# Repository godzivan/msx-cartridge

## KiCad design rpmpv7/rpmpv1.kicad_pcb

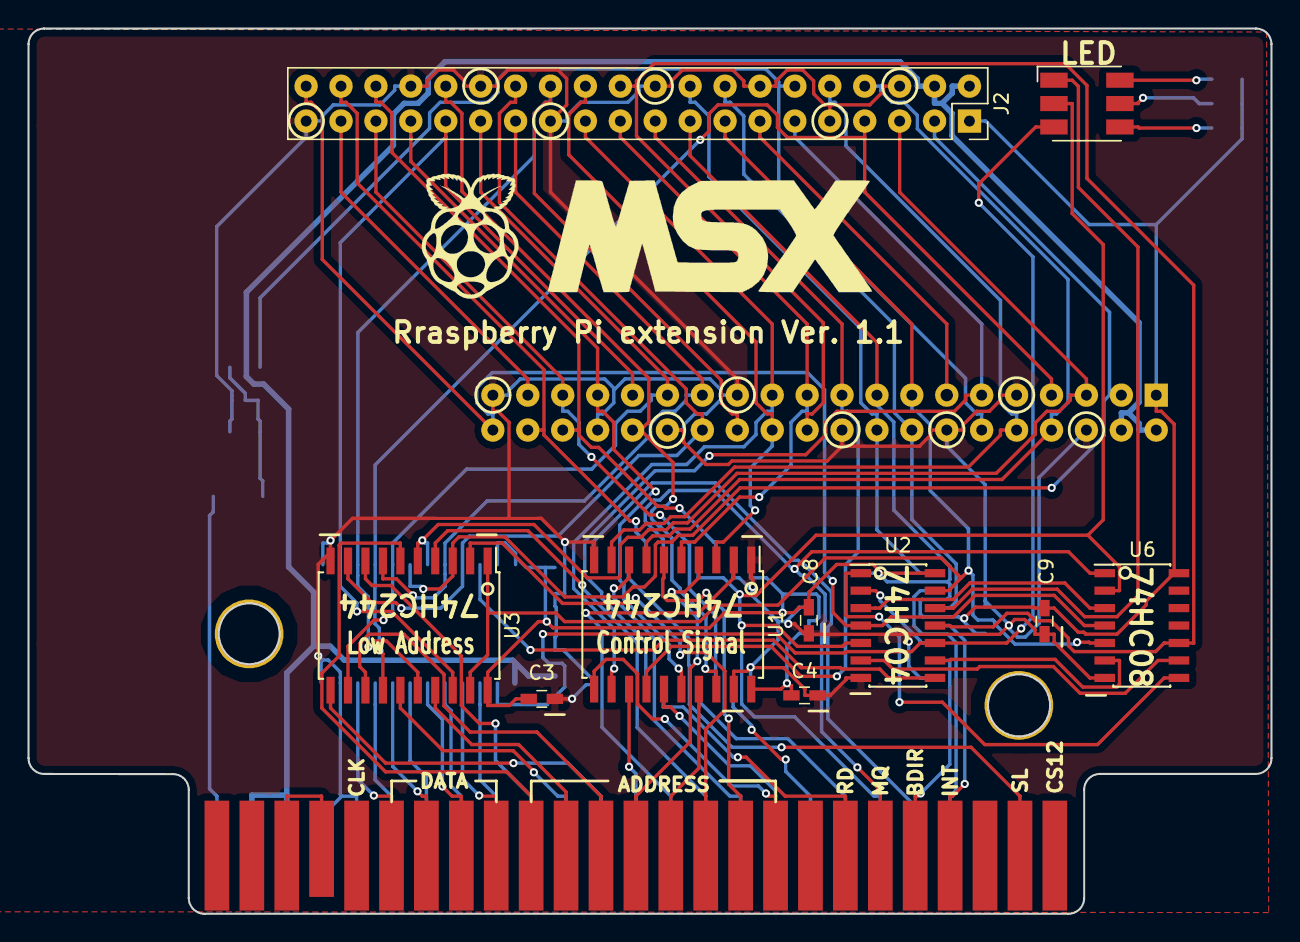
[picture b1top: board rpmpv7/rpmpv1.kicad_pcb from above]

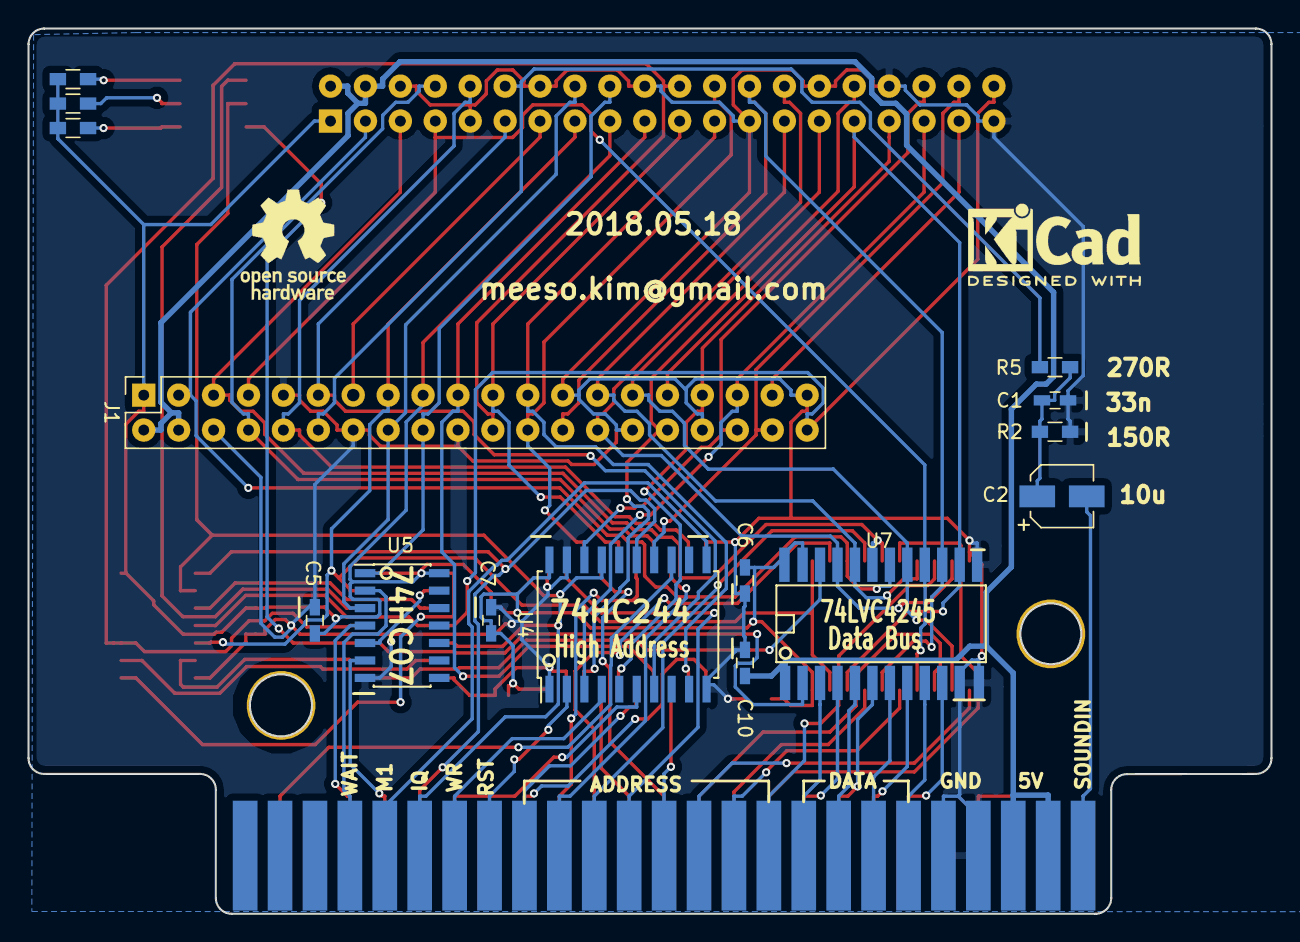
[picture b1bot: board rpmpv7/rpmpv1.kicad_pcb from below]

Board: 2 copper layers, 90.4 x 64.4 mm, 29 parts (17 on the bottom side), 79 nets.

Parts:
C1, C3, C4, C5, C6, C7, C8, C9, C10: C; C_0603_HandSoldering
C2: CP; CP_Elec_4x4.5
D1: LED_RGB; LED_RGB_5050-6
G1: LOGO; raspberry_pi_logo
J1, J2: RPi_GPIO; Socket_Strip_Straight_2x20_Pitch2.54mm
P1: CONN_02X25; card_edge_connector
R1, R2, R3, R4, R5: R; R_0603_HandSoldering
REF2: OSHW-Logo_7.5x8mm_SilkScreen
REF3: KiCad-Logo2_6mm_SilkScreen
U1, U3, U4: 74HC244; SOIC-20W_7.5x12.8mm_Pitch1.27mm
U2: 74HC04; SOIC-14_3.9x8.7mm_Pitch1.27mm
U5: 74LS07; SOIC-14_3.9x8.7mm_Pitch1.27mm
U6: 74LS08; SOIC-14_3.9x8.7mm_Pitch1.27mm
U7: LVC4245; SOIC-24@

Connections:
+3V3: C3.1, C4.1, C5.1, C6.1, C7.1, C8.1, C9.1, J1.1, J1.17, J2.1, J2.17, R1.1, R3.1, R4.1, U1.20, U2.14, U3.20, U4.20, U5.14, U6.14, U7.23, U7.24
+5V: C10.2, J1.2, J1.4, J2.2, J2.4, P1.45, P1.47, U7.1
/A0: P1.28, U3.13
/A1: P1.27, U3.11
/A2: P1.30, U3.17
/A3: P1.29, U3.15
/A4: P1.32, U3.6
/A5: P1.31, U3.8
/A6: P1.22, U3.2
/A7: P1.21, U3.4
/A8: P1.24, U1.17
/A9: P1.17, U1.15
/A10: P1.20, U1.6
/A11: P1.19, U1.8
/A12: P1.23, U1.2
/A13: P1.26, U1.4
/A14: P1.25, U1.13
/A15: P1.18, U1.11
/ATN: J1.40, J2.40, U2.4, U6.4
/BDIR: U2.2, U5.5
/BUSDIR: P1.10, U5.6
/D0: P1.34, U7.4
/D1: P1.33, U7.3
/D2: P1.36, U7.6
/D3: P1.35, U7.5
/D4: P1.38, U7.8
/D5: P1.37, U7.7
/D6: P1.40, U7.10
/D7: P1.39, U7.9
/DAT_DIR: D1.3, U2.10, U7.2
/DAT_EN: U2.8, U7.22
/INT: P1.8, U5.4
/IORQ: D1.2, P1.11, U2.5, U4.17, U6.2
/M1: P1.9, U4.11
/MREQ: P1.12, U4.15, U6.1
/RA8: J1.24, J2.24, U1.3
/RA9: J1.21, J2.21, U1.5
/RA10: J1.19, J2.19, U1.14
/RA11: J1.23, J2.23, U1.12
/RA12: J1.32, J2.32, U1.18
/RA13: J1.33, J2.33, U1.16
/RA14: J1.8, J2.8, U1.7
/RA15: J1.10, J2.10, U1.9
/RATN: J1.15, J2.15, U2.13, U3.1, U3.19, U6.5
/RC16: J1.36, J2.36, U4.18
/RC17: J1.11, J2.11, U4.7
/RC18: J1.12, J2.12, R5.1
/RC19: J1.35, J2.35, U4.3
/RC20: J1.38, J2.38, U4.14
/RC23: J1.16, J2.16, U5.3
/RC24: J1.18, J2.18, U5.1
/RC25: J1.22, J2.22, U2.11, U6.10
/RC26: J1.37, J2.37
/RC27: J1.13, J2.13
/RD: P1.14, U4.6
/RD0: J1.27, J2.27, U3.7, U7.20
/RD1: J1.28, J2.28, U3.9, U7.21
/RD2: J1.3, J2.3, U3.3, U7.18
/RD3: J1.5, J2.5, U3.5, U7.19
/RD4: J1.7, J2.7, U3.14, U7.16
/RD5: J1.29, J2.29, U3.12, U7.17
/RD6: J1.31, J2.31, U3.18, U7.14
/RD7: J1.26, J2.26, U3.16, U7.15
/RESET: P1.15, U4.2
/SLTSL: P1.4, U4.13
/SOUNDIN: C2.2, P1.49
/WAIT: P1.7, U5.2
/WR: P1.13, U4.4
/nATN: U2.3, U6.3
/nBDIR: U2.1, U6.8
/nDAT_EN: U2.9, U6.6
/nIORQ: U2.6, U6.9
/nRATN: D1.1, U2.12
GND: C1.2, C3.2, C4.2, C5.2, C6.2, C7.2, C8.2, C9.2, C10.1, J1.6, J1.9, J1.14, J1.20, J1.25, J1.30, J1.34, J1.39, J2.6, J2.9, J2.14, J2.20, J2.25, J2.30, J2.34, J2.39, P1.41, P1.43, R2.2, U1.1, U1.10, U1.19, U2.7, U3.10, U4.1, U4.10, U4.19, U5.7, U6.7, U7.11, U7.12, U7.13
unnamed: C1.1, C2.1, R2.1, R5.2
unnamed: D1.4, R4.2
unnamed: D1.5, R3.2
unnamed: D1.6, R1.2
unnamed: P1.44, P1.46

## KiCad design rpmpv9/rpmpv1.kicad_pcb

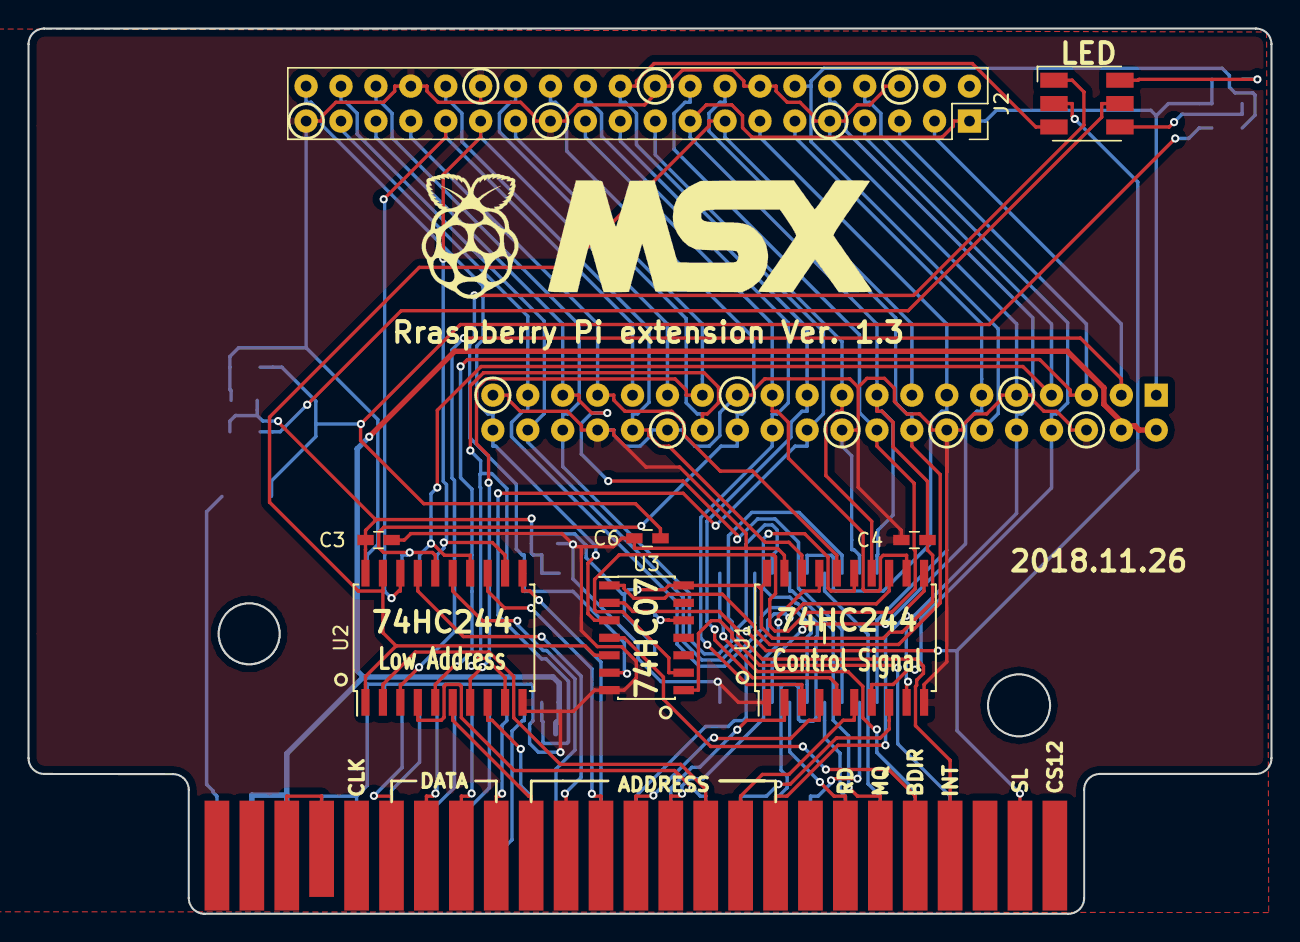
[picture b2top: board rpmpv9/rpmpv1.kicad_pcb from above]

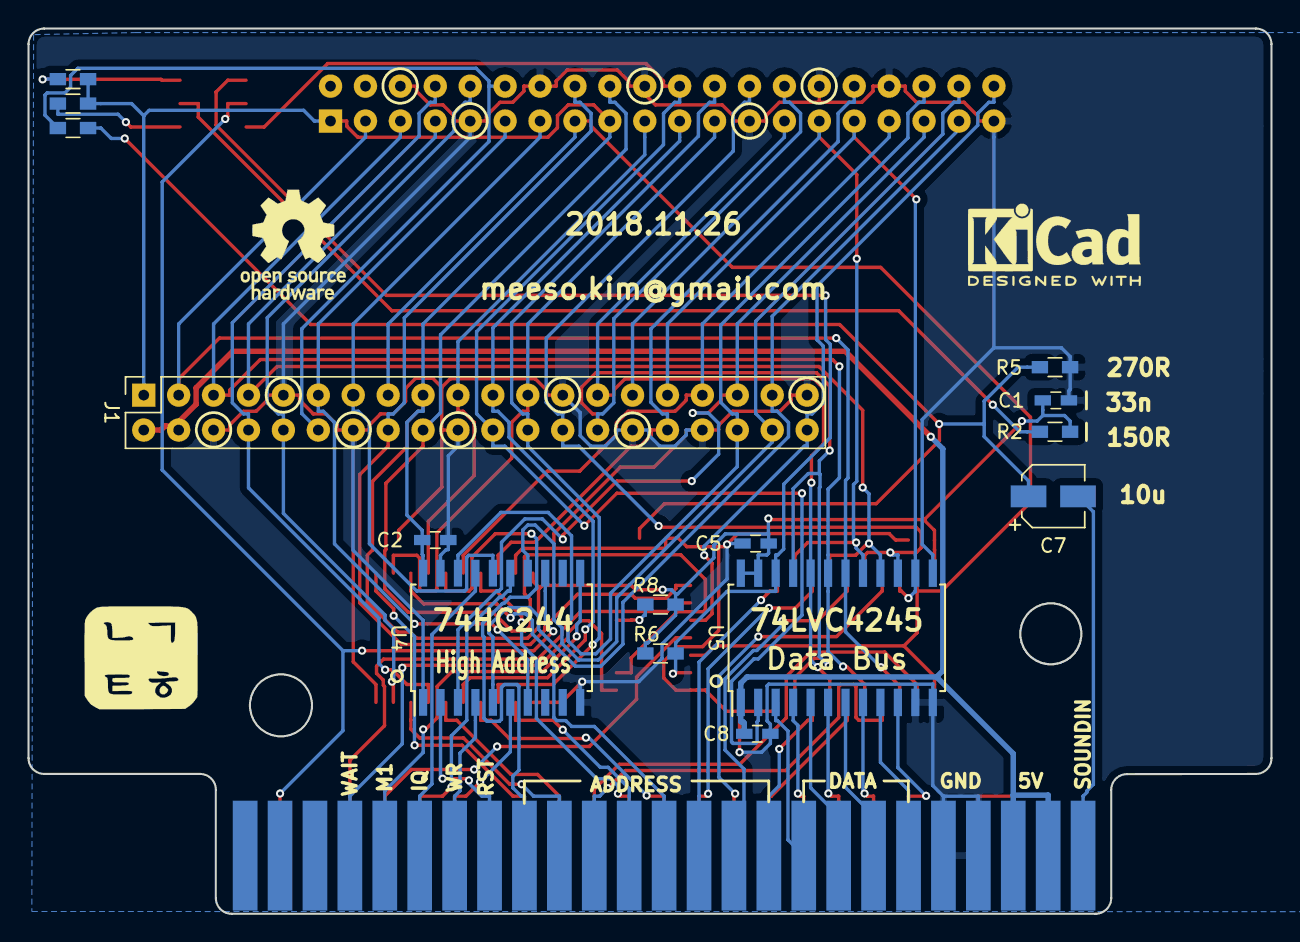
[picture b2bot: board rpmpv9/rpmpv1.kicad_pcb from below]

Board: 2 copper layers, 90.4 x 64.4 mm, 28 parts (17 on the bottom side), 73 nets.

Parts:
C1, C2, C3, C4, C5, C6, C8: C; C_0603_HandSoldering
C7: CP; CP_Elec_4x4.5
D1: LED_RGB; LED_RGB_5050-6
G1: LOGO; raspberry_pi_logo
G2: LOGO; msx-logo
J1, J2: RPi_GPIO; Socket_Strip_Straight_2x20_Pitch2.54mm
P1: CONN_02X25; card_edge_connector
R1, R2, R3, R4, R5, R6, R8: R; R_0603_HandSoldering
REF2: OSHW-Logo_7.5x8mm_SilkScreen
REF3: KiCad-Logo2_6mm_SilkScreen
U1, U2, U4: 74HC244; SOIC-20W_7.5x12.8mm_Pitch1.27mm
U3: 74LS07; SOIC-14_3.9x8.7mm_Pitch1.27mm
U5: LVC4245; SOIC-24W_7.5x15.4mm_Pitch1.27mm

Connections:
+3V3: C1.1, C2.1, C3.1, C4.1, C5.1, J1.1, J1.17, J2.1, J2.17, R1.2, R2.2, R3.2, R6.1, R8.1, U1.20, U2.20, U3.14, U4.20, U5.23, U5.24
+5V: C8.2, J1.2, J1.4, P1.45, P1.47, U5.1
/A0: P1.28, U2.13
/A1: P1.27, U2.11
/A2: P1.30, U2.17
/A3: P1.29, U2.15
/A4: P1.32, U2.6
/A5: P1.31, U2.8
/A6: P1.22, U2.2
/A7: P1.21, U2.4
/A8: P1.24, U1.17
/A9: P1.17, U1.15
/A10: P1.20, U1.6
/A11: P1.19, U1.8
/A12: P1.23, U1.2
/A13: P1.26, U1.4
/A14: P1.25, U1.13
/A15: P1.18, U1.11
/ADDR: J1.15, J2.15, U2.1, U2.19, U3.5
/BUSDIR: P1.10, U3.4
/D0: P1.34, U5.4
/D1: P1.33, U5.3
/D2: P1.36, U5.6
/D3: P1.35, U5.5
/D4: P1.38, U5.8
/D5: P1.37, U5.7
/D6: P1.40, U5.10
/D7: P1.39, U5.9
/DAT_DIR: D1.3, J1.22, J2.22, U5.2
/DAT_EN: D1.1, R6.2, U3.6, U5.22
/EXTRA: R8.2, U3.12
/INT: P1.8, U3.2
/IORQ: P1.11, U4.17
/M1: P1.9, U4.11
/MREQ: P1.12, U4.15
/RA8: J1.24, J2.24, U1.3
/RA9: J1.21, J2.21, U1.5
/RA10: J1.19, J2.19, U1.14
/RA11: J1.23, J2.23, U1.12
/RA12: J1.32, J2.32, U1.18
/RA13: J1.33, J2.33, U1.16
/RA14: J1.8, J2.8, U1.7
/RA15: J1.10, J2.10, U1.9
/RC16: J1.36, J2.36, U4.18
/RC17: J1.11, J2.11, U4.7
/RC18: J1.12, J2.12, R4.1
/RC19: J1.35, J2.35, U4.3
/RC20: J1.38, J2.38, U4.14
/RC21: J1.40, J2.40, U3.3
/RC23: J1.16, J2.16, U3.1
/RC24: J1.18, J2.18, U3.9
/RC26: J1.37, J2.37, U4.5
/RC27: J1.13, J2.13, U4.16
/RD: P1.14, U4.6
/RD0: J1.27, J2.27, U2.7, U5.20
/RD1: J1.28, J2.28, U2.9, U5.21
/RD2: J1.3, J2.3, U2.3, U5.18
/RD3: J1.5, J2.5, U2.5, U5.19
/RD4: J1.7, J2.7, U2.14, U5.16
/RD5: J1.29, J2.29, U2.12, U5.17
/RD6: J1.31, J2.31, U2.18, U5.14
/RD7: J1.26, J2.26, U2.16, U5.15
/RESET: P1.15, U4.2
/SLTSL: D1.2, P1.4, U4.13
/SOUNDIN: C7.2, P1.49
/WAIT: P1.7, U3.8
/WR: P1.13, U4.4
GND: C1.2, C2.2, C3.2, C4.2, C5.2, C6.2, C8.1, J1.6, J1.9, J1.14, J1.20, J1.25, J1.30, J1.34, J1.39, J2.6, J2.9, J2.14, J2.20, J2.25, J2.30, J2.34, J2.39, P1.41, P1.43, R5.2, U1.1, U1.10, U1.19, U2.10, U3.7, U4.1, U4.10, U4.19, U5.11, U5.12, U5.13
unnamed: C6.1, C7.1, R4.2, R5.1
unnamed: D1.4, R3.1
unnamed: D1.5, R2.1
unnamed: D1.6, R1.1
unnamed: P1.44, P1.46

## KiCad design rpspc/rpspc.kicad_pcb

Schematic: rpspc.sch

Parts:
J1: RPi_GPIO; Pin_Header_Straight_2x20_Pitch2.54mm
J2: Conn_02x17_Top_Bottom; Pin_Header_Straight_2x17_Pitch2.54mm
U1, U2: 74LS245; DIP-20_W7.62mm

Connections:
+5V: J1.2, J1.4, J2.33, U1.20, U2.20
/A0: J2.13, U1.16
/A1: J2.11, U1.17
/A2: J2.9
/A3: J2.7
/A4: J2.5
/A5: J2.3
/A6: J2.1, U1.12
/A7: J2.4
/A8: J2.6
/A9: J2.8
/A10: J2.12
/A11: J2.10, U1.18
/A12: J2.2
/CLK: J2.27, U1.13
/D0: J2.15, U2.16
/D1: J2.17, U2.14
/D2: J2.19, U2.12
/D3: J2.21, U2.11
/D4: J2.20, U2.13
/D5: J2.18, U2.15
/D6: J2.16, U2.17
/D7: J2.14, U2.18
/EXT1: J2.26, U1.14, U2.19
/RA0: J1.15, U1.4
/RA1: J1.16, U1.3
/RA2: J1.18, U1.2
/RA4: J1.22, U1.8
/RCLK: J1.12, U1.7
/RD0: J1.27, U2.4
/RD1: J1.28, U2.6
/RD2: J1.3, U2.8
/RD3: J1.5, U2.9
/RD4: J1.7, U2.7
/RD5: J1.29, U2.5
/RD6: J1.31, U2.3
/RD7: J1.26, U2.2
/RESET: J2.23, U1.15
/REXT1: J1.11, U1.6
/RRESET: J1.13, U1.5
/RWR: J1.8, U1.9
/WR: J2.31, U1.11, U2.1
GND: J1.6, J1.9, J1.14, J1.20, J1.25, J1.30, J1.34, J1.39, J2.34, U1.1, U1.10, U1.19, U2.10

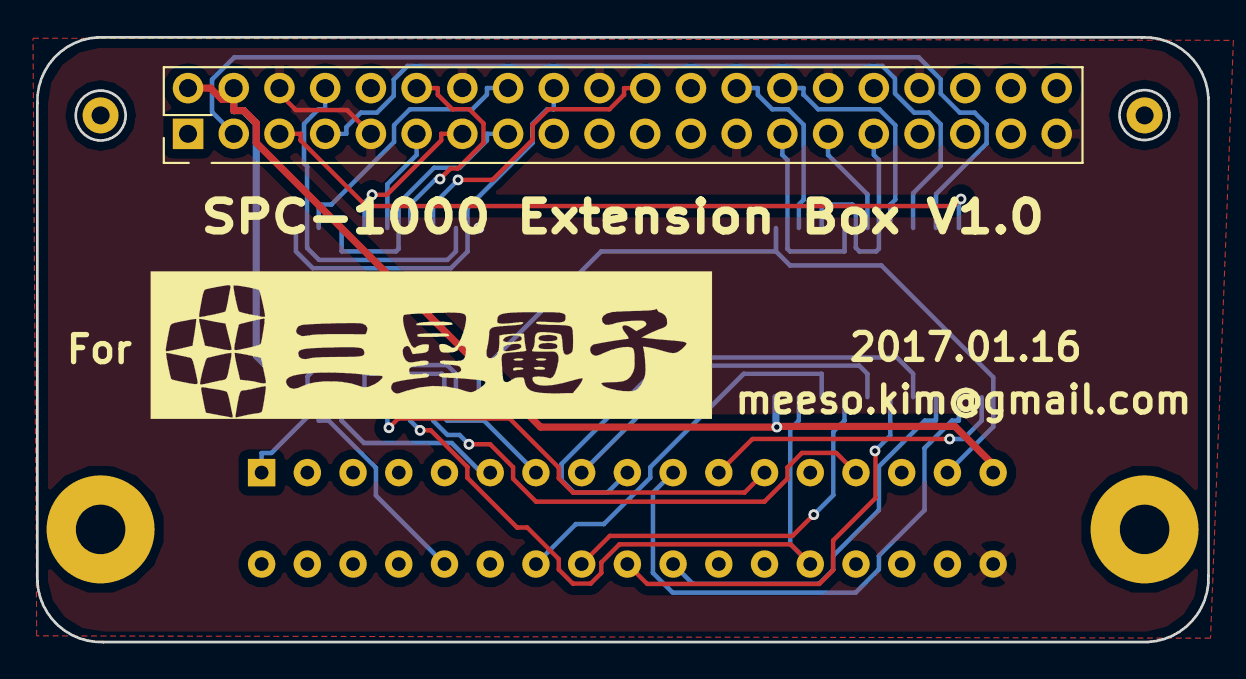
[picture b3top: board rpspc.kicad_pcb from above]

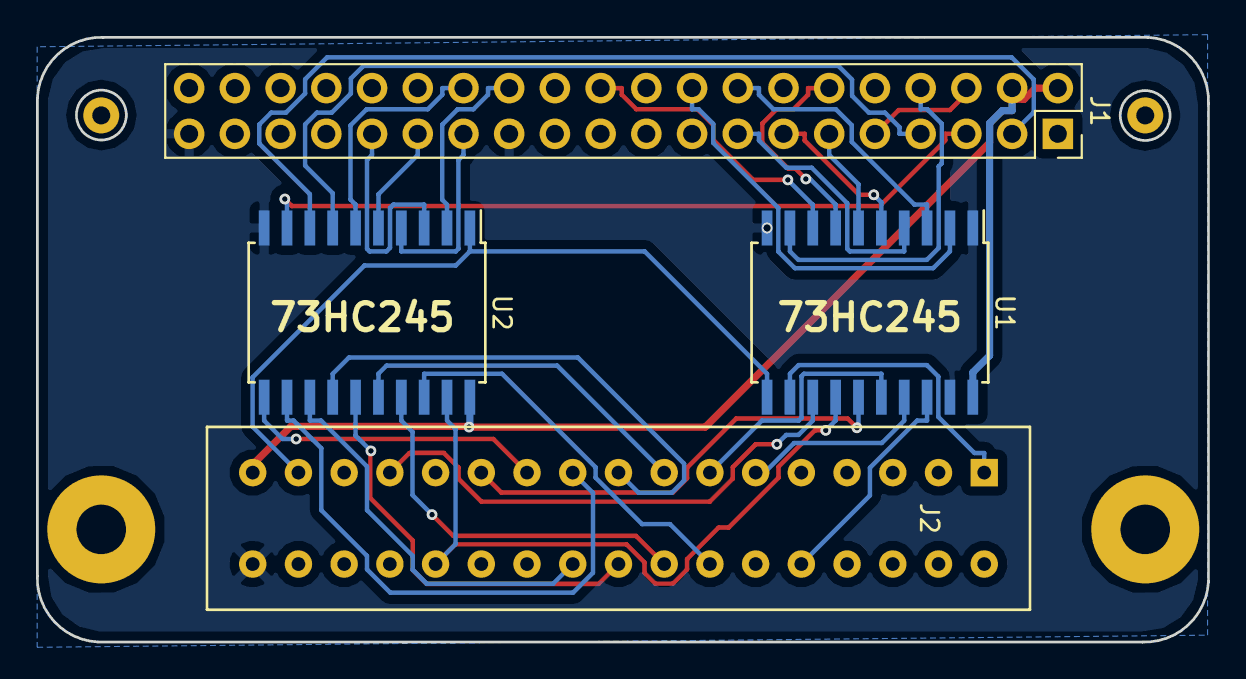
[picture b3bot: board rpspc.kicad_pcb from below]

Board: 2 copper layers, 65.1 x 33.6 mm, 4 parts (4 on the bottom side), 34 nets.

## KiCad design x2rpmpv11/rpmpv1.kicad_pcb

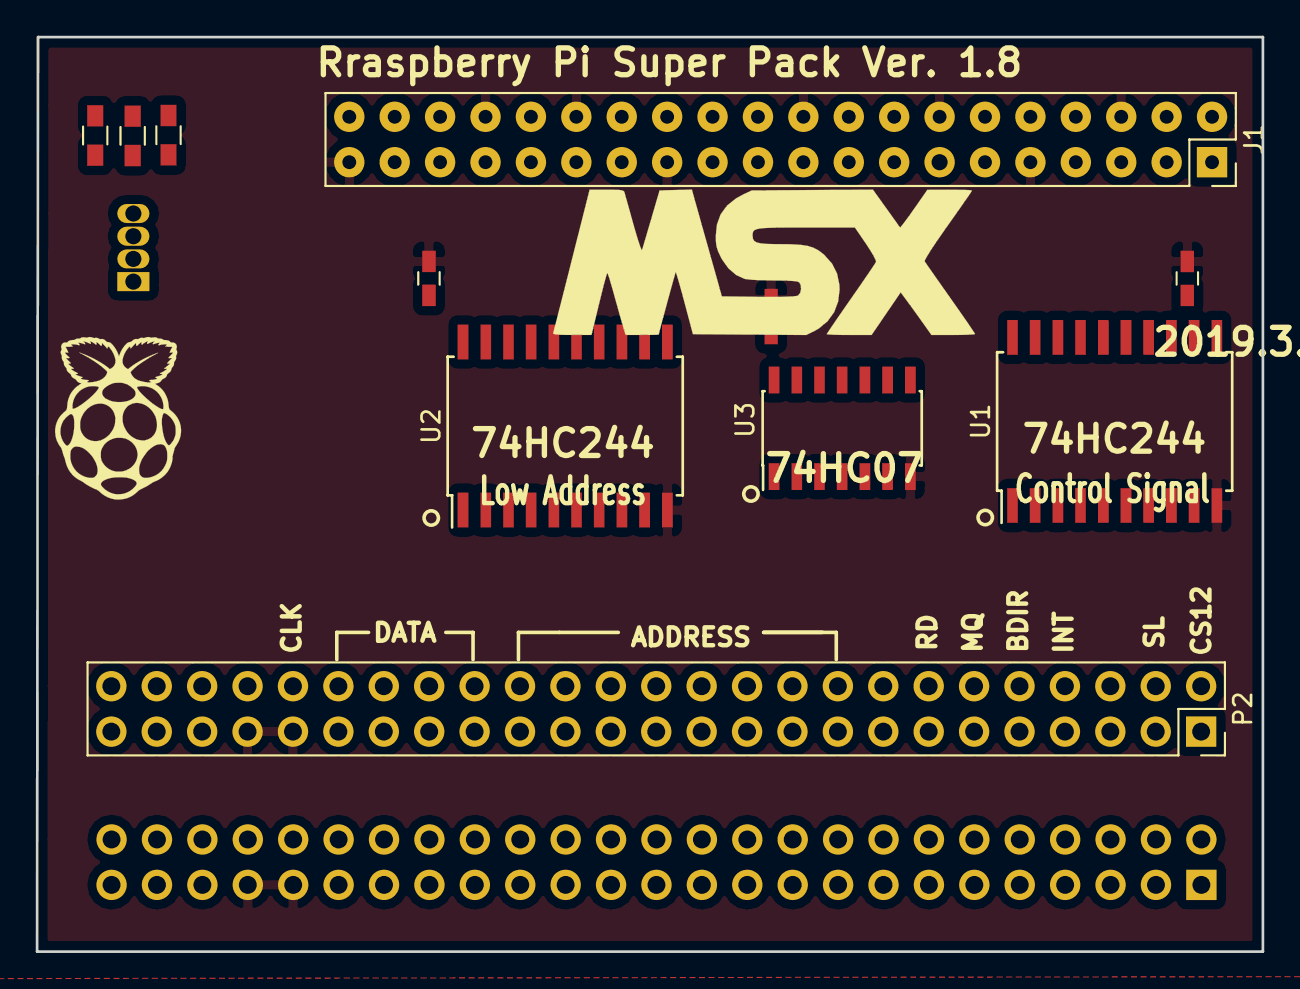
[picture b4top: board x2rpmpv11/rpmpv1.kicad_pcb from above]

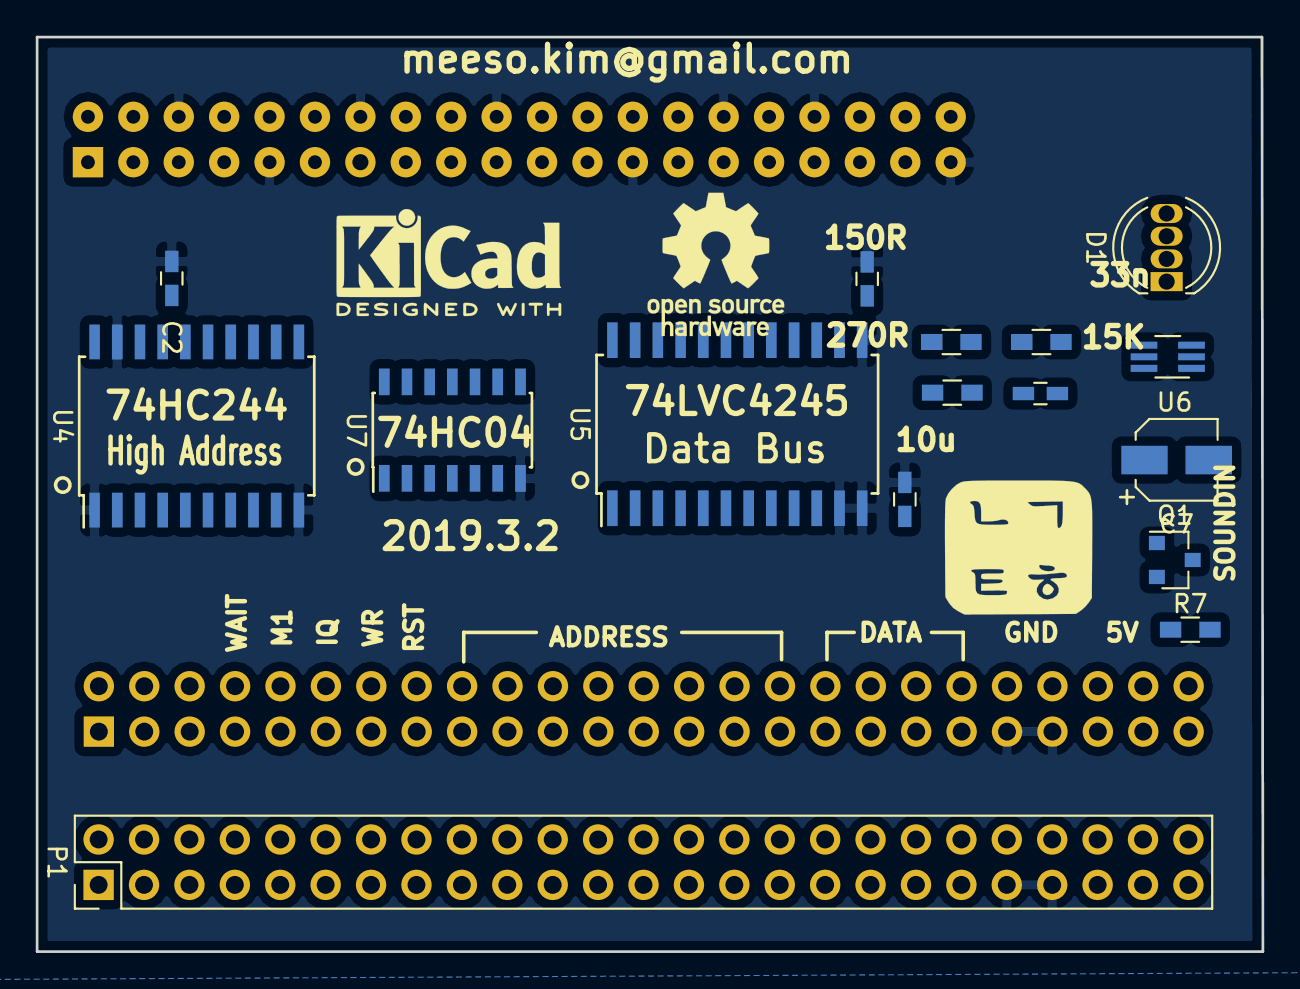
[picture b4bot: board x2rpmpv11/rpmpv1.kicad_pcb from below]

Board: 2 copper layers, 68.6 x 51.2 mm, 31 parts (18 on the bottom side), 85 nets, no tracks yet.

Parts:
C1, C2, C3, C4, C5, C6, C8: C; C_0603_HandSoldering
C7: CP; CP_Elec_4x4.5
D1: LED_RABG; LED_D5.0mm-4
G1: LOGO; raspberry_pi_logo
G2: LOGO; msx-logo
J1: RPi_GPIO; Socket_Strip_Straight_2x20_Pitch2.54mm
P1: CONN_02X25; Pin_Header_Straight_2x25_Pitch2.54mm
P2: CONN_02X25; Socket_Strip_Straight_2x25_Pitch2.54mm
Q1: Q_NPN_BEC; SOT-23
R1, R2, R3, R4, R5, R6, R7: R; R_0603_HandSoldering
REF2: OSHW-Logo_7.5x8mm_SilkScreen
REF3: KiCad-Logo2_6mm_SilkScreen
U1, U2, U4: 74HC244; SOIC-20W_7.5x12.8mm_Pitch1.27mm
U3: 74LS07; SOIC-14_3.9x8.7mm_Pitch1.27mm
U5: LVC4245; SOIC-24W_7.5x15.4mm_Pitch1.27mm
U6: NC7WZ16; SOT-363_SC-70-6_Handsoldering
U7: 74HC04; SOIC-14_3.9x8.7mm_Pitch1.27mm

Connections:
+3V3: C1.1, C2.1, C3.1, C4.1, C5.1, D1.2, J1.1, J1.17, U1.20, U2.20, U3.14, U4.20, U5.23, U5.24, U6.5, U7.14
+5V: C8.2, J1.2, J1.4, P1.45, P1.47, P2.45, P2.47, R6.1, U5.1
/12V+: P1.48, P2.48
/12V-: P1.50, P2.50
/A0: P1.28, P2.28, U2.13
/A1: P1.27, P2.27, U2.11
/A2: P1.30, P2.30, U2.17
/A3: P1.29, P2.29, U2.15
/A4: P1.32, P2.32, U2.6
/A5: P1.31, P2.31, U2.8
/A6: P1.22, P2.22, U2.2
/A7: P1.21, P2.21, U2.4
/A8: P1.24, P2.24, U1.2
/A9: P1.17, P2.17, U1.4
/A10: P1.20, P2.20, U1.6
/A11: P1.19, P2.19, U1.8
/A12: P1.23, P2.23, U1.17
/A13: P1.26, P2.26, U1.15
/A14: P1.25, P2.25, U1.13
/A15: P1.18, P2.18, U1.11
/ADDR: J1.15, U1.1, U1.19, U2.1, U2.19, U7.1
/BUSDIR: P1.10, P2.10, U3.4
/CLK: P1.42, P2.42, U4.2
/CS1: P1.1, P2.1
/CS2: P1.3, P2.3
/CS12: P1.2, P2.2
/D0: P1.34, P2.34, U5.4
/D1: P1.33, P2.33, U5.3
/D2: P1.36, P2.36, U5.6
/D3: P1.35, P2.35, U5.5
/D4: P1.38, P2.38, U5.8
/D5: P1.37, P2.37, U5.7
/D6: P1.40, P2.40, U5.10
/D7: P1.39, P2.39, U5.9
/DAT_DIR: J1.22, R3.1, U5.2
/DAT_EN: R1.1, U5.22, U7.2
/INT: P1.8, P2.8, U3.2
/IORQ: P1.11, P2.11, U4.17
/M1: P1.9, P2.9, U4.4
/MREQ: P1.12, P2.12, U4.15
/RA8: J1.24, U1.18
/RA9: J1.21, U1.16
/RA10: J1.19, U1.14
/RA11: J1.23, U1.12
/RA12: J1.32, U1.3
/RA13: J1.33, U1.5
/RA14: J1.8, U1.7
/RA15: J1.10, U1.9
/RC16: J1.36, U4.9
/RC17: J1.11, U4.7
/RC18: J1.12, U6.1
/RC19: J1.35, U4.3
/RC20: J1.38, U4.12
/RC21: J1.40, U3.3
/RC23: J1.16, U3.1
/RC24: J1.18, R2.1, U3.9
/RC26: J1.37, U4.5
/RC27: J1.13, U4.14
/RD: P1.14, P2.14, U4.8
/RD0: J1.27, U2.7, U5.20
/RD1: J1.28, U2.9, U5.21
/RD2: J1.3, U2.3, U5.18
/RD3: J1.5, U2.5, U5.19
/RD4: J1.7, U2.14, U5.16
/RD5: J1.29, U2.12, U5.17
/RD6: J1.31, U2.18, U5.14
/RD7: J1.26, U2.16, U5.15
/RESET: P1.15, P2.15, U4.11
/RFSH: P1.6, P2.6
/RSV0: P1.5, P2.5
/RSV1: P1.16, P2.16
/SLTSL: P1.4, P2.4, U4.13
/SOUNDIN: P1.49, P2.49, R7.1
/SW0: P1.44, P2.44
/SW1: P1.46, P2.46
/WAIT: P1.7, P2.7, U3.8
/WR: P1.13, P2.13, U4.6
GND: C1.2, C2.2, C3.2, C4.2, C5.2, C8.1, J1.6, J1.9, J1.14, J1.20, J1.25, J1.30, J1.34, J1.39, P1.41, P1.43, P2.41, P2.43, U1.10, U2.10, U3.7, U4.1, U4.10, U4.19, U5.11, U5.12, U5.13, U6.2, U7.7
unnamed: C6.1, C7.1, R4.2, R5.1
unnamed: C7.2, Q1.1, R6.2
unnamed: D1.1, R1.2
unnamed: D1.3, R3.2
unnamed: D1.4, R2.2
unnamed: Q1.3, R7.2
unnamed: R4.1, U6.6
